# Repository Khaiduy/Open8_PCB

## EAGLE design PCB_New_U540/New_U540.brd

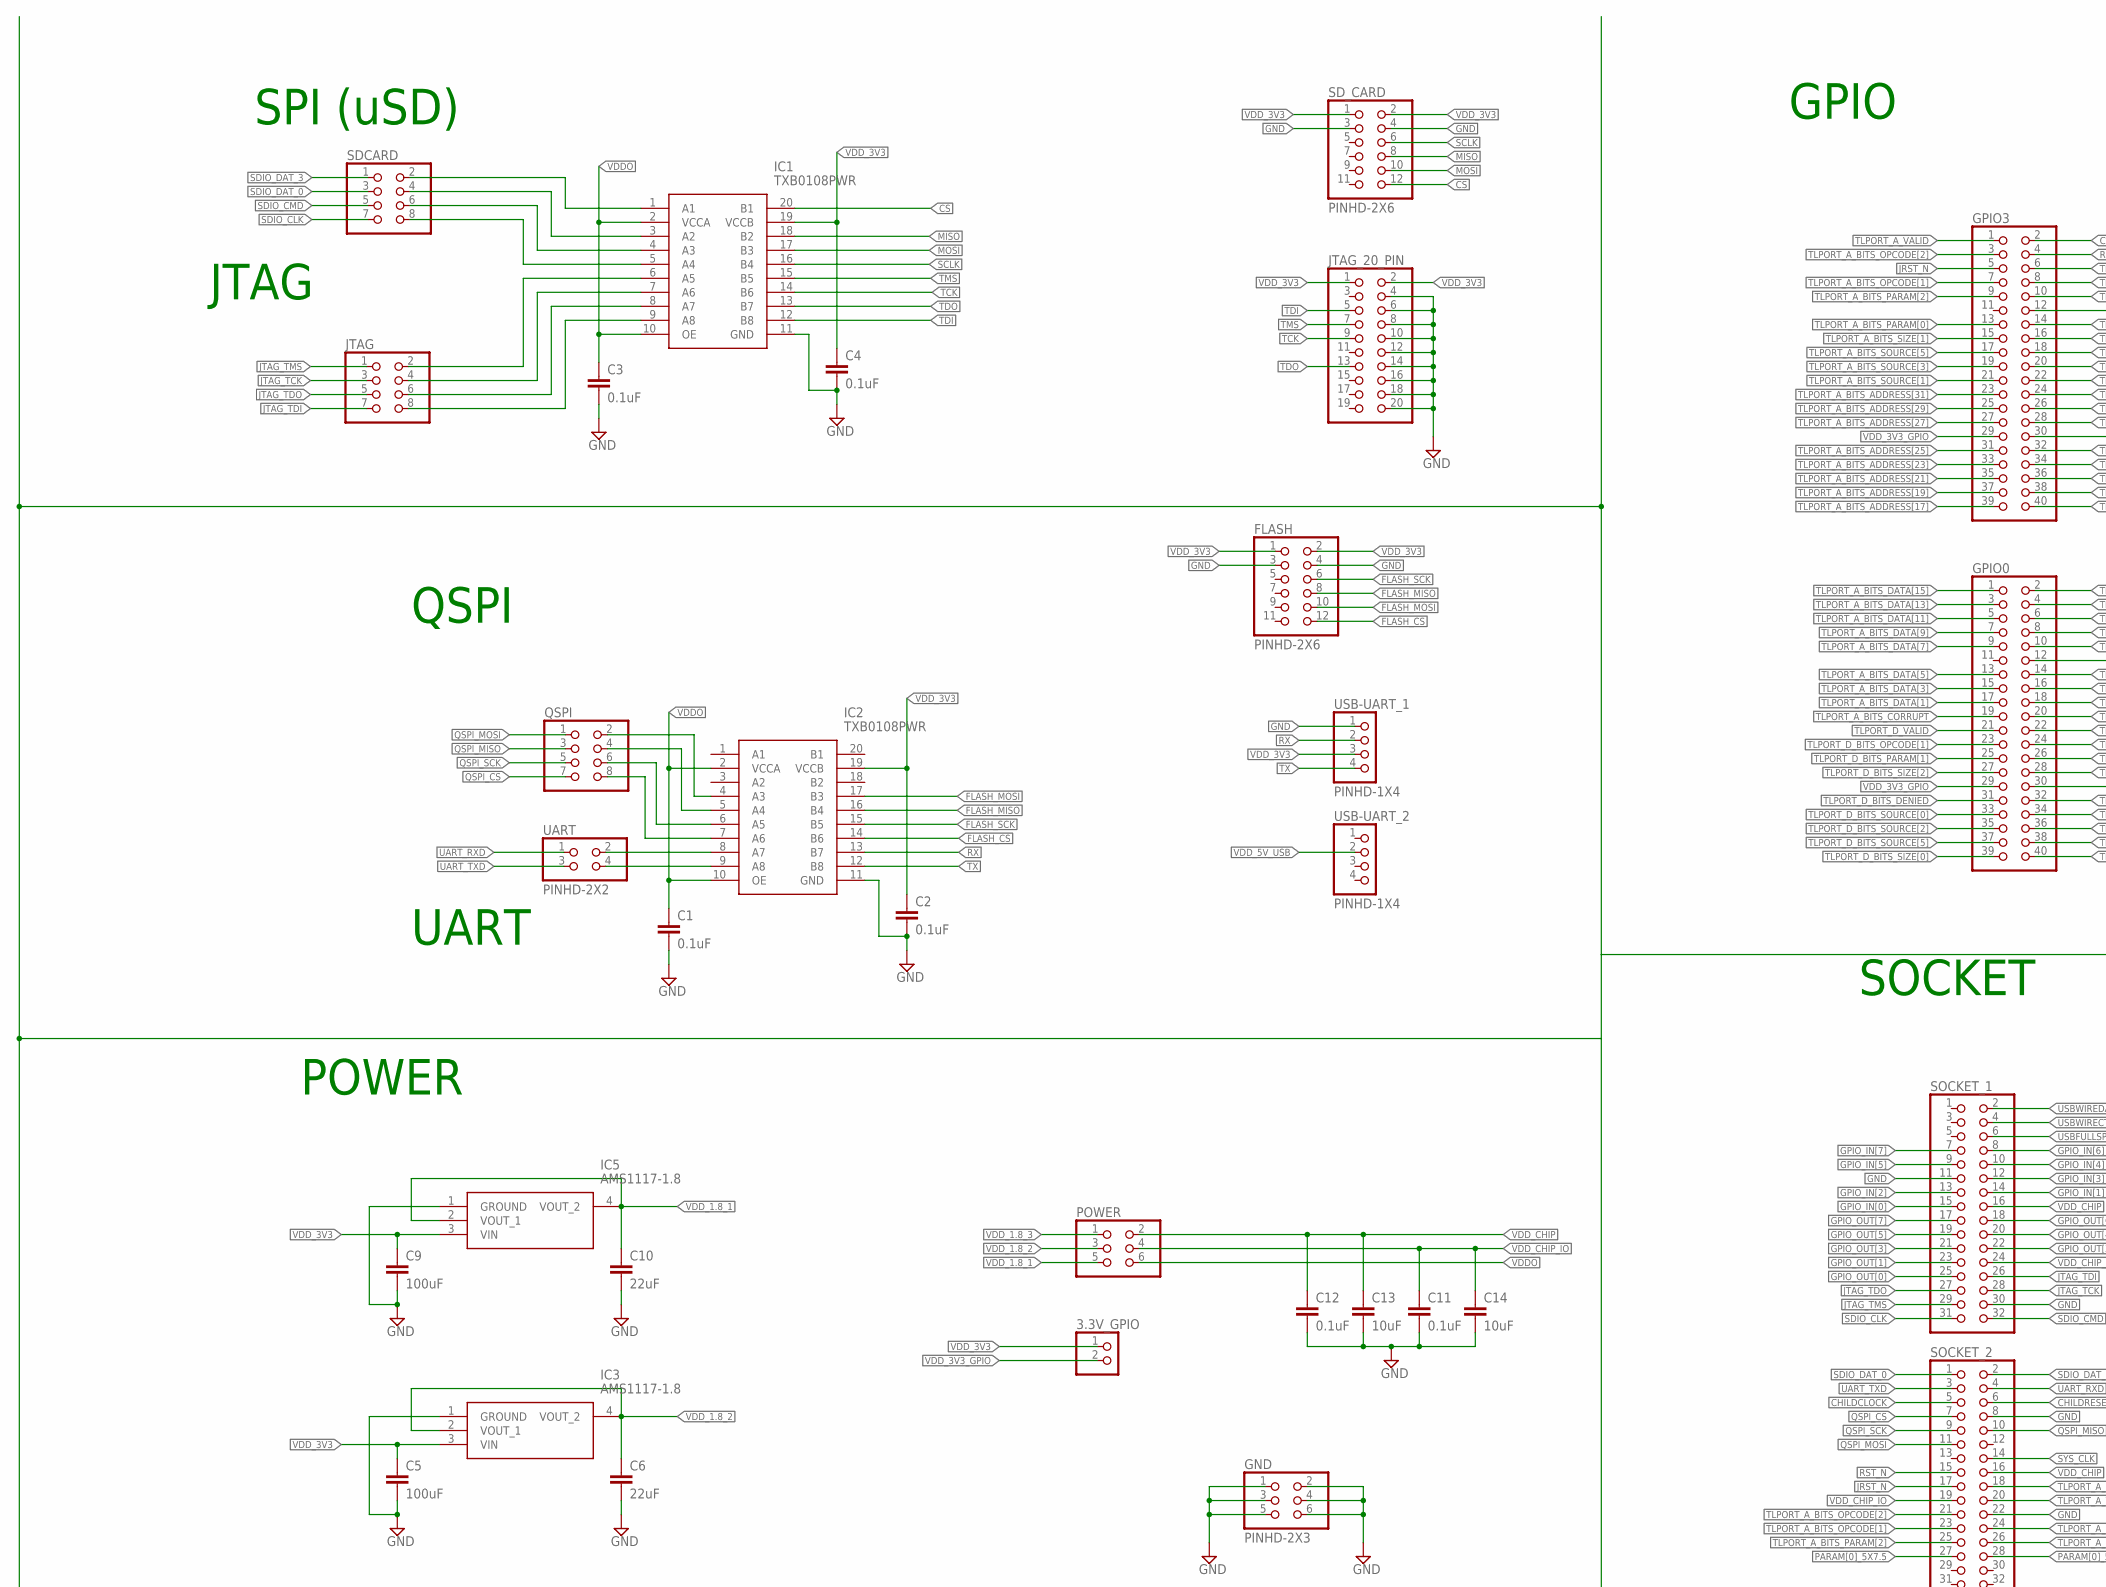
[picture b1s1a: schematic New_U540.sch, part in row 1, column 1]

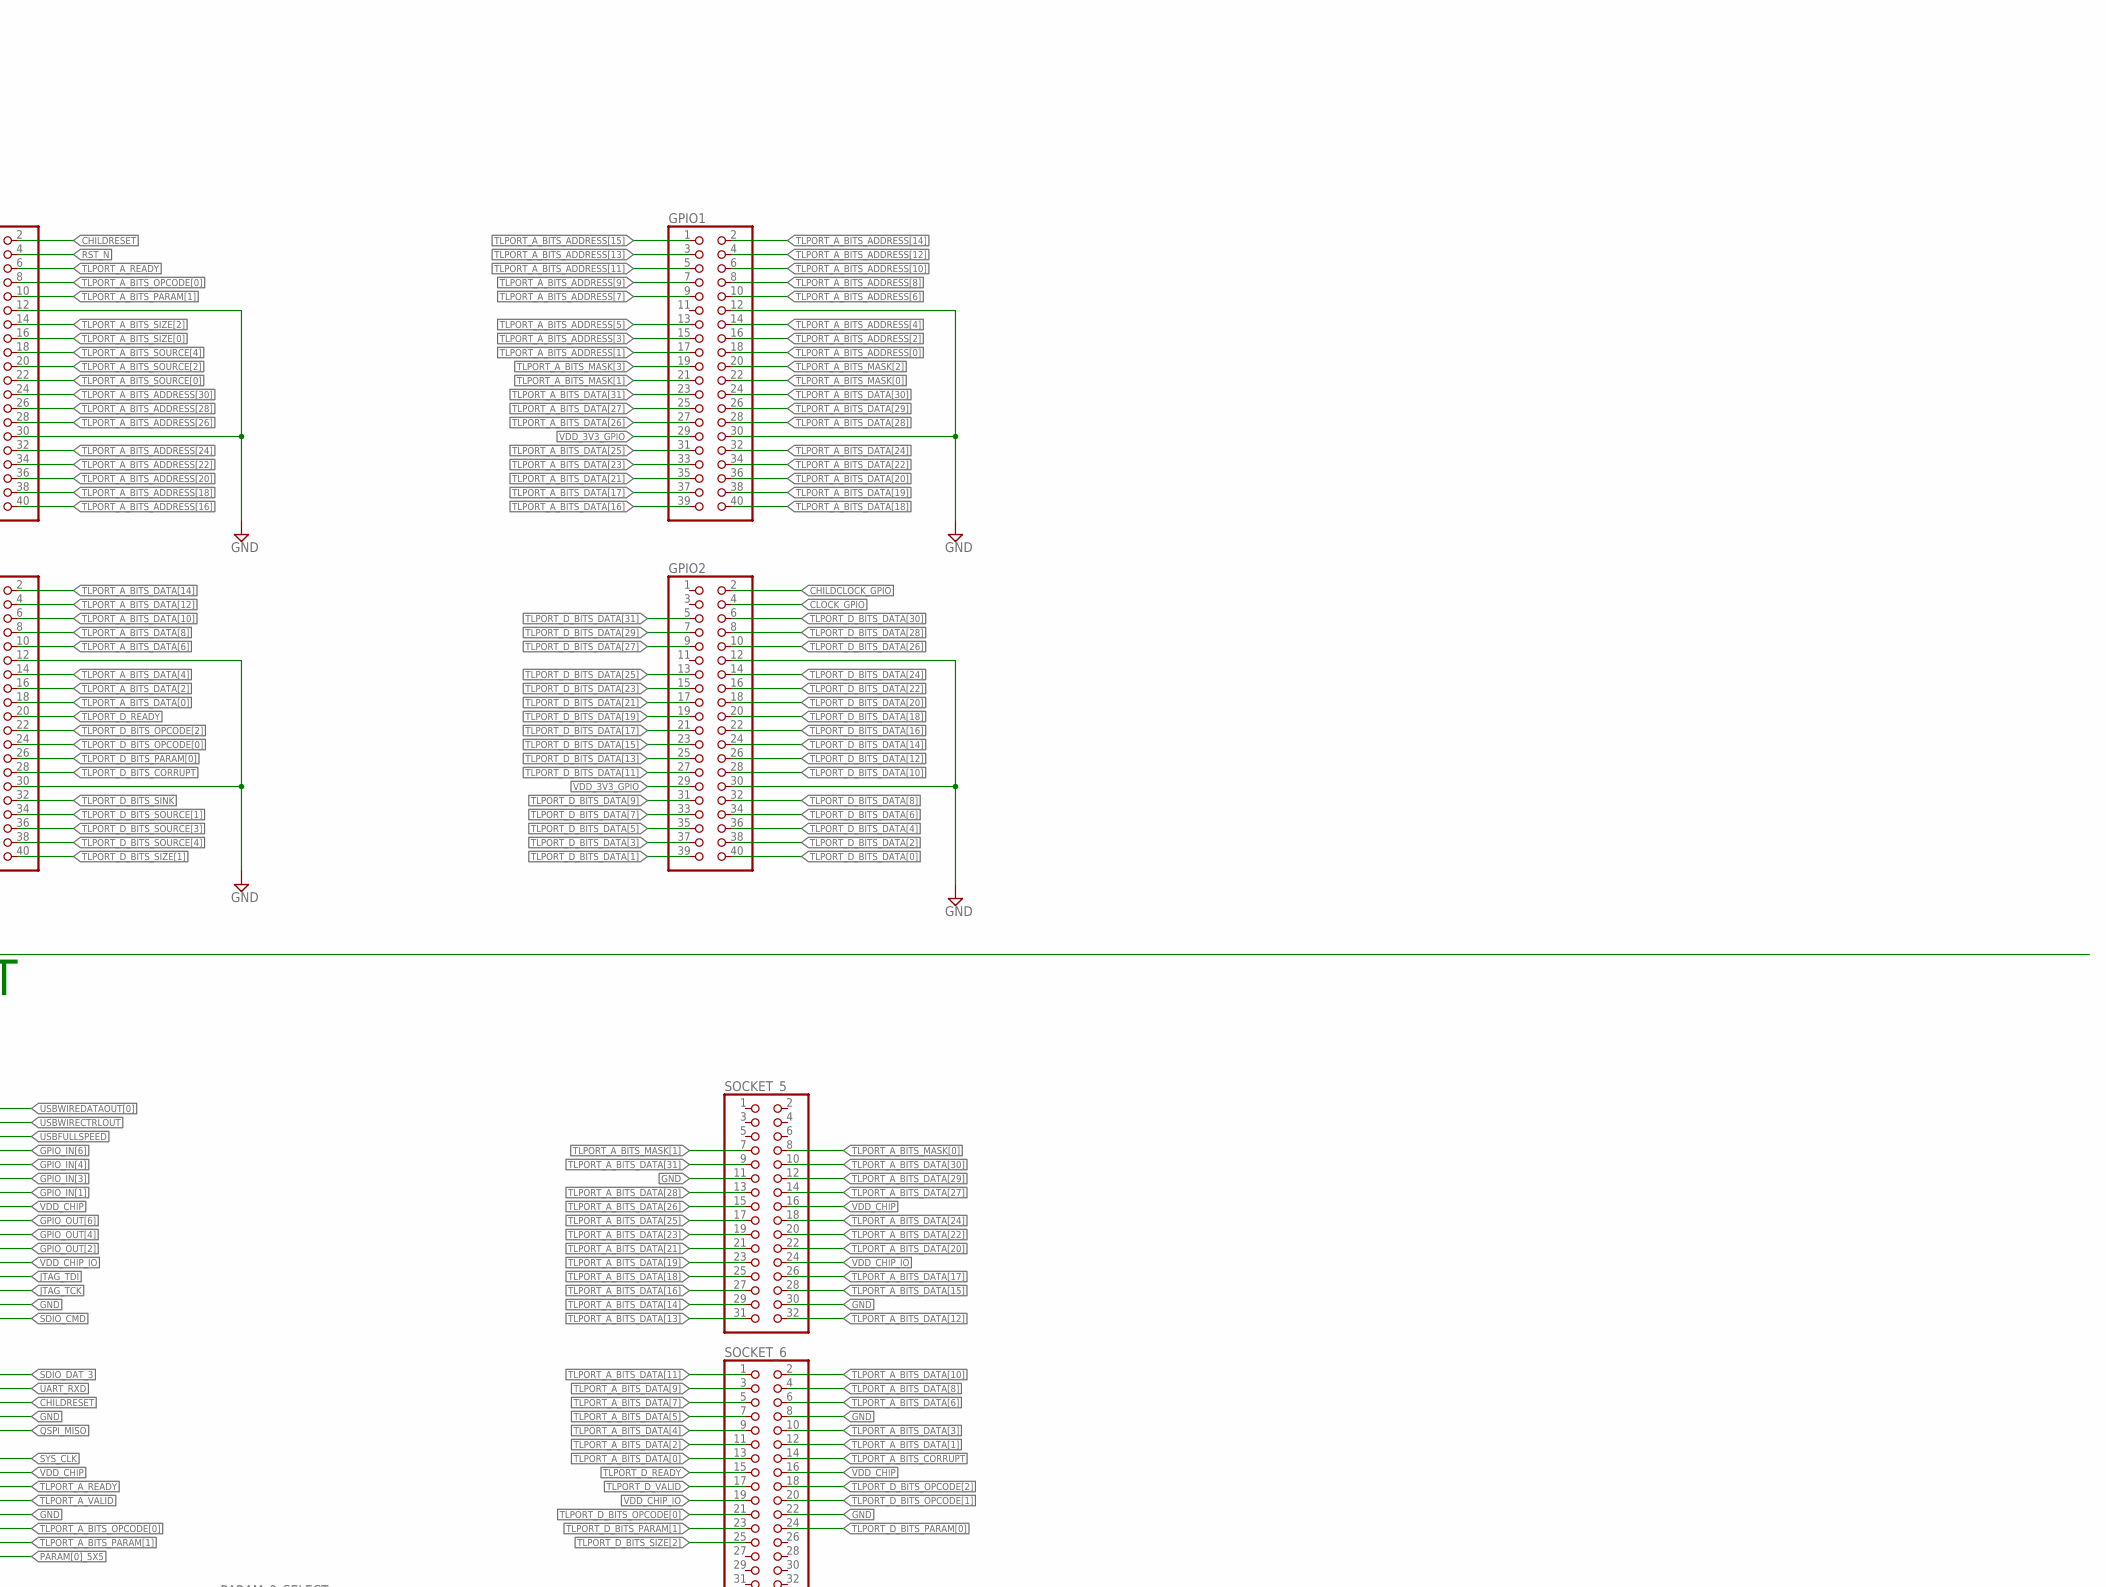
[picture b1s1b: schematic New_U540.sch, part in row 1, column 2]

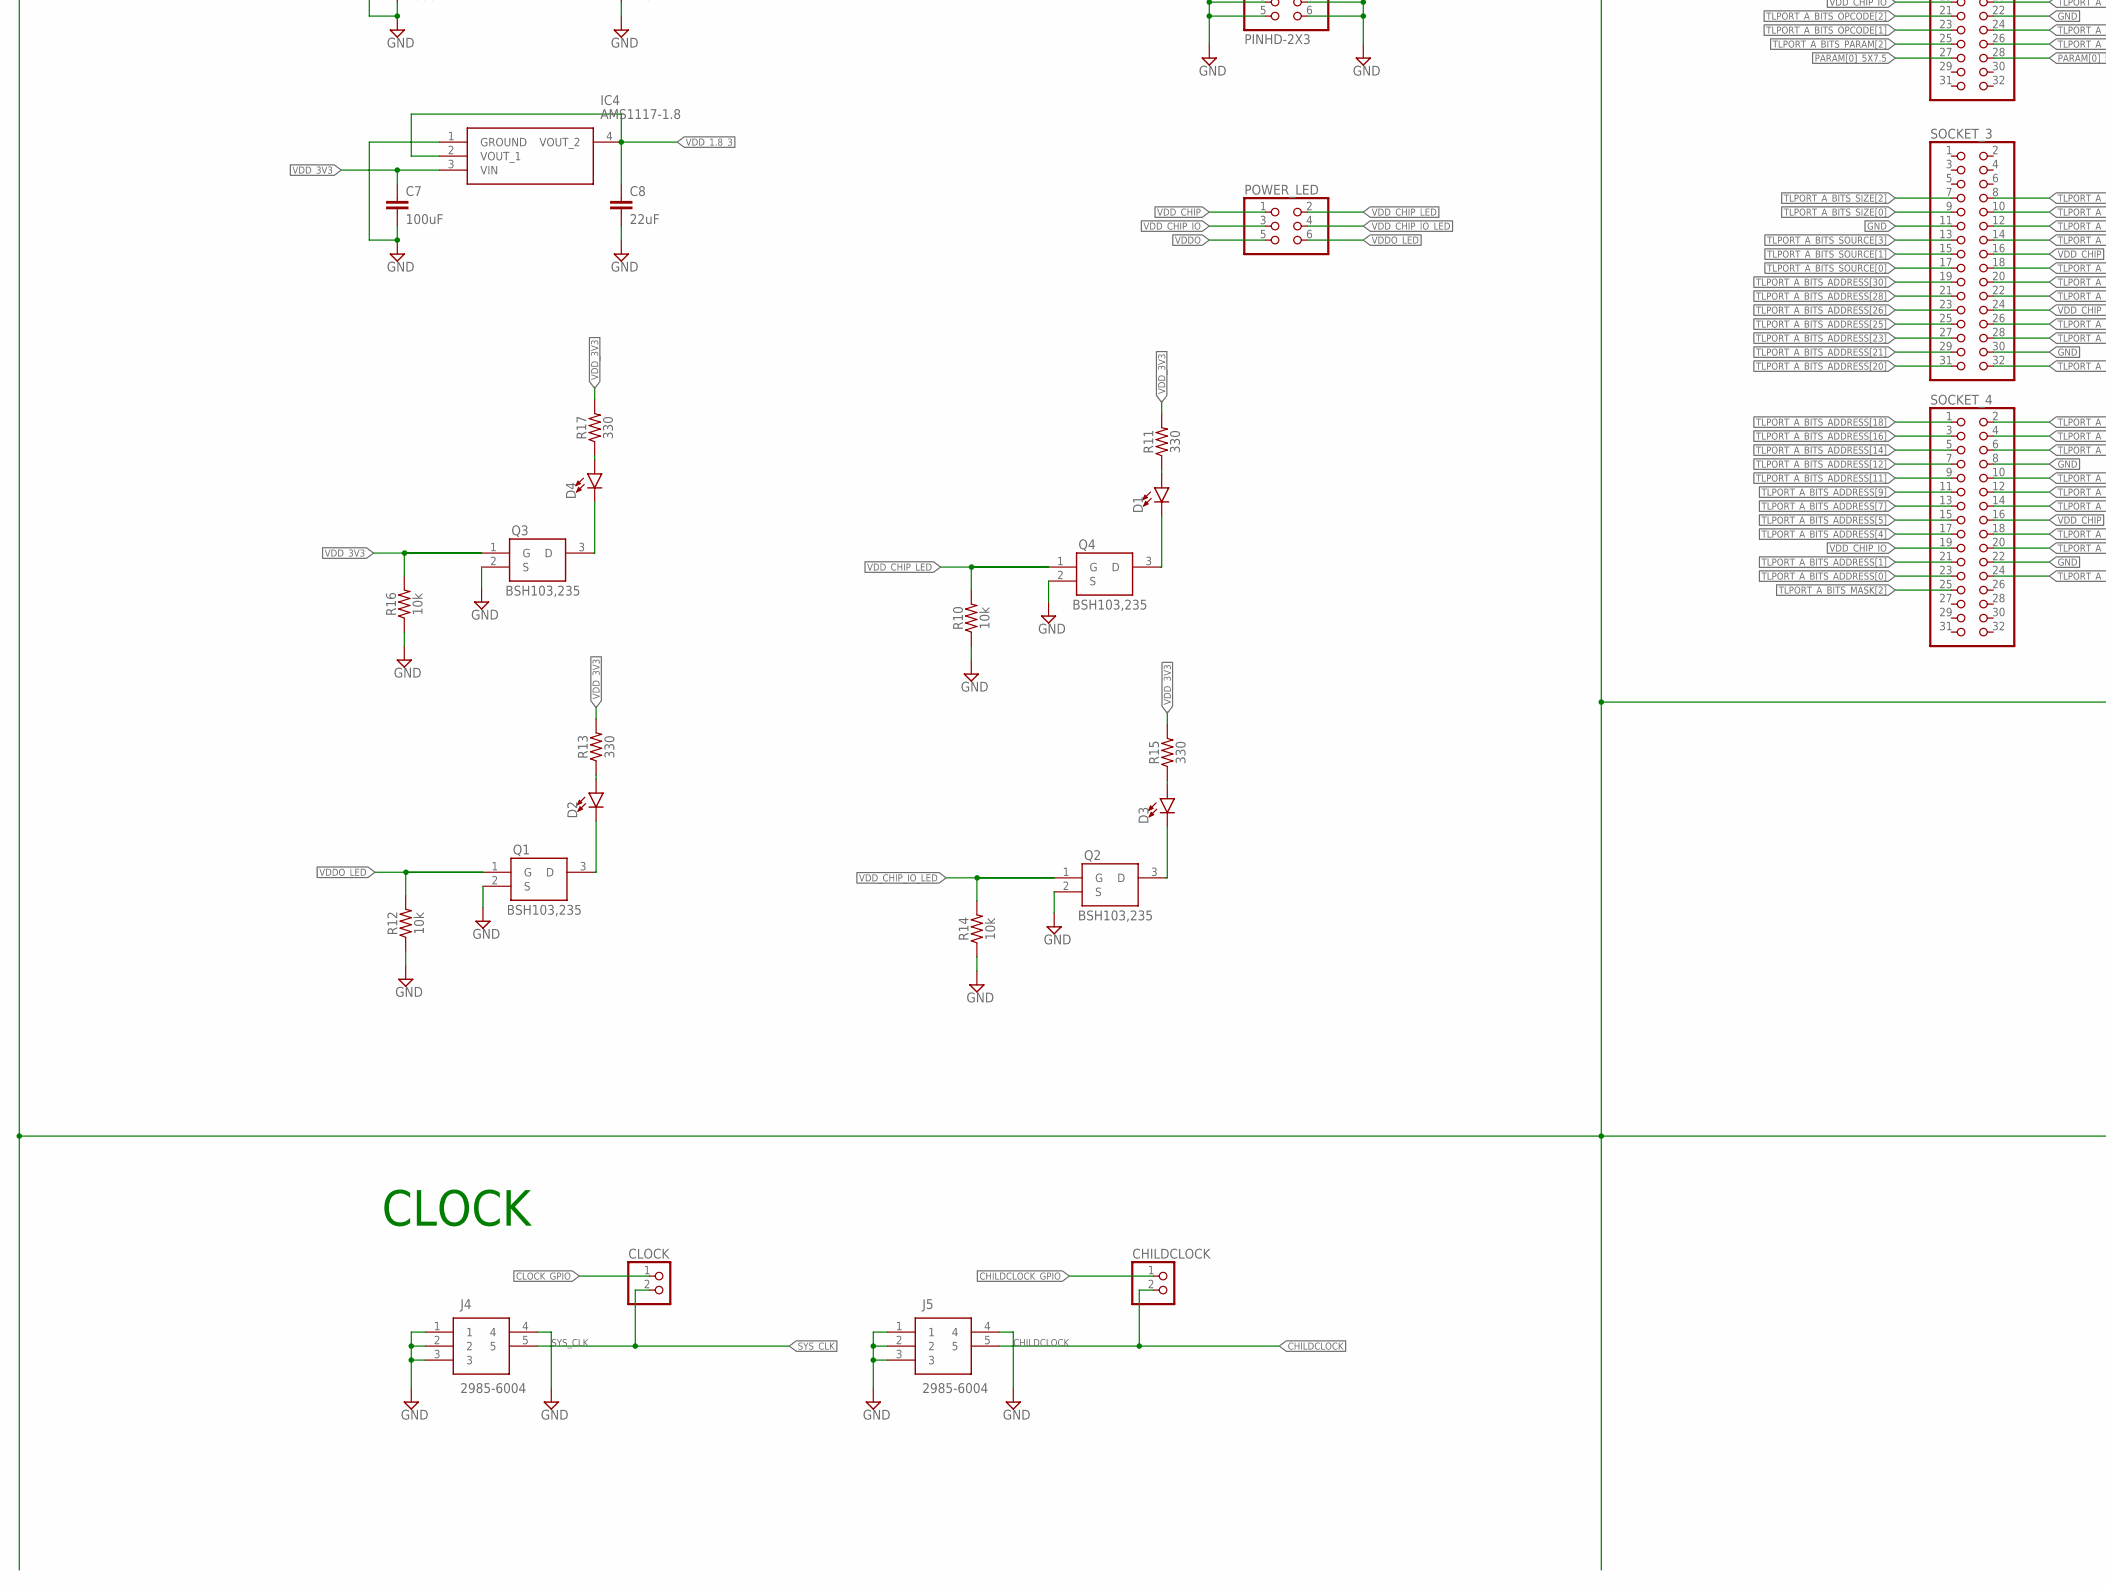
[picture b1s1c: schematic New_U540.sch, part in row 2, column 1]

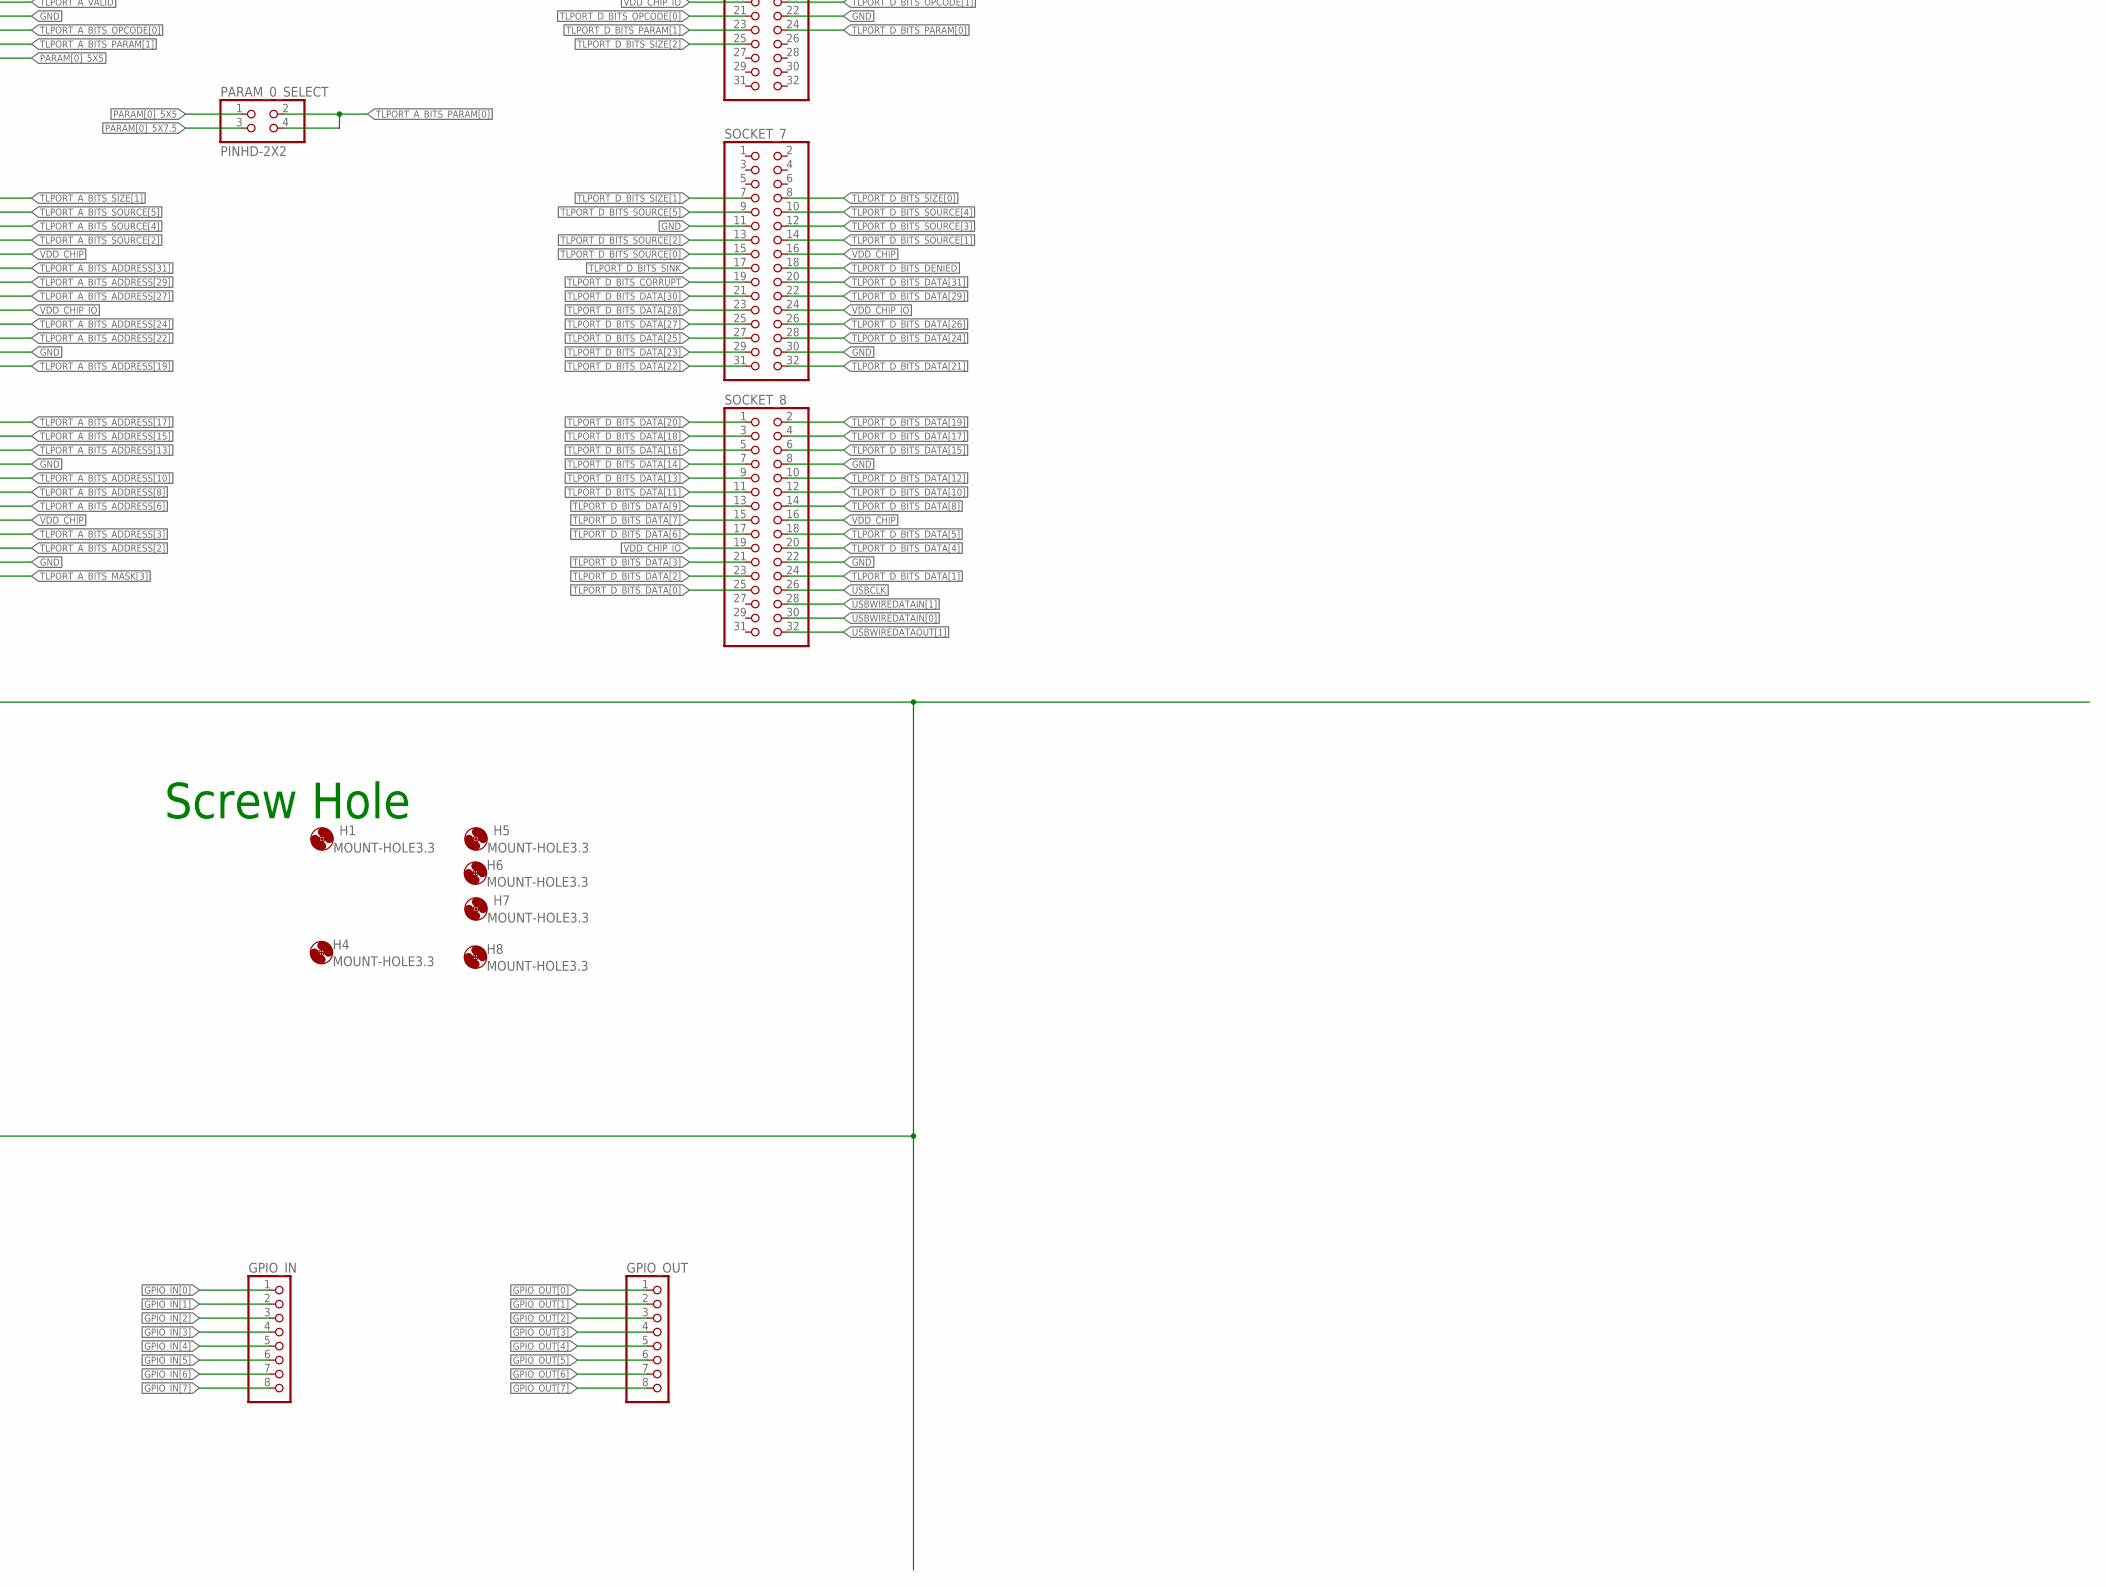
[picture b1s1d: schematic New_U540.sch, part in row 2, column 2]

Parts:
3.3V_GPIO: PINHD-1X2; 1X02
C1, C2, C3, C4, C11, C12: 0.1uF; 1206
C5, C7, C9: 100uF; 1206
C6, C8, C10: 22uF; 1206
C13, C14: 10uF; 1206
CHILDCLOCK: PINHD-1X2; 1X02
CLOCK: PINHD-1X2; 1X02
D1, D2, D3, D4: LED1206; LED-1206
FLASH: PINHD-2X6; 2X06
GND: PINHD-2X3; 2X03
GPIO0, GPIO1, GPIO2, GPIO3: PINHD-2X20; 2X20
GPIO_IN: PINHD-1X8; 1X08
GPIO_OUT: PINHD-1X8; 1X08
H1, H4, H5, H6, H7, H8: MOUNT-HOLE3.3; 3,3
IC1, IC2: TXB0108PWR; SOP65P640X120-20N
IC3, IC4, IC5: AMS1117-1.8; SOT229P700X180-4N
J4, J5: 2985-6004; 29856004
JTAG: PINHD-2X4; 2X04
JTAG_20_PIN: PINHD-2X10; 2X10
PARAM_0_SELECT: PINHD-2X2; 2X02
POWER: PINHD-2X3; 2X03
POWER_LED: PINHD-2X3; 2X03
Q1, Q2, Q3, Q4: BSH103,235; SOT95P230X110-3N
QSPI: PINHD-2X4; 2X04
R10, R12, R14, R16: 10k; 1206
R11, R13, R15, R17: 330; 1206
SDCARD: PINHD-2X4; 2X04
SD_CARD: PINHD-2X6; 2X06
SOCKET_1, SOCKET_2, SOCKET_3, SOCKET_4, SOCKET_5, SOCKET_6, SOCKET_7, SOCKET_8: PINHD-2X16; 2X16
UART: PINHD-2X2; 2X02
USB-UART_1, USB-UART_2: PINHD-1X4; 1X04

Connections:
CHILDCLOCK: CHILDCLOCK.2, J5.5, SOCKET_2.5
CHILDCLOCK_GPIO: CHILDCLOCK.1, GPIO2.2
CHILDRESET: GPIO3.2, SOCKET_2.6
CLOCK_GPIO: CLOCK.1, GPIO2.4
CS: IC1.20 (B1), SD_CARD.12
FLASH_CS: FLASH.12, IC2.14 (B6)
FLASH_MISO: FLASH.8, IC2.16 (B4)
FLASH_MOSI: FLASH.10, IC2.17 (B3)
FLASH_SCK: FLASH.6, IC2.15 (B5)
GND: C1.2, C2.2, C3.2, C4.2, C5.2, C6.2, C7.2, C8.2, C9.2, C10.2, C11.2, C12.2, C13.2, C14.2, FLASH.3, FLASH.4, GND.1, GND.2, GND.3, GND.4, GND.5, GND.6, GPIO0.12, GPIO0.30, GPIO1.12, GPIO1.30, GPIO2.12, GPIO2.30, GPIO3.12, GPIO3.30, IC1.11 (GND), IC2.11 (GND), IC3.1 (GROUND), IC4.1 (GROUND), IC5.1 (GROUND), J4.1, J4.2, J4.3, J4.4, J5.1, J5.2, J5.3, J5.4, JTAG_20_PIN.4, JTAG_20_PIN.6, JTAG_20_PIN.8, JTAG_20_PIN.10, JTAG_20_PIN.12, JTAG_20_PIN.14, JTAG_20_PIN.16, JTAG_20_PIN.18, JTAG_20_PIN.20, Q1.2 (S), Q2.2 (S), Q3.2 (S), Q4.2 (S), R10.1, R12.1, R14.1, R16.1, SD_CARD.3, SD_CARD.4, SOCKET_1.11, SOCKET_1.30, SOCKET_2.8, SOCKET_2.22, SOCKET_3.11, SOCKET_3.30, SOCKET_4.8, SOCKET_4.22, SOCKET_5.11, SOCKET_5.30, SOCKET_6.8, SOCKET_6.22, SOCKET_7.11, SOCKET_7.30, SOCKET_8.8, SOCKET_8.22, USB-UART_1.1
GPIO_IN[0]: GPIO_IN.1, SOCKET_1.15
GPIO_IN[1]: GPIO_IN.2, SOCKET_1.14
GPIO_IN[2]: GPIO_IN.3, SOCKET_1.13
GPIO_IN[3]: GPIO_IN.4, SOCKET_1.12
GPIO_IN[4]: GPIO_IN.5, SOCKET_1.10
GPIO_IN[5]: GPIO_IN.6, SOCKET_1.9
GPIO_IN[6]: GPIO_IN.7, SOCKET_1.8
GPIO_IN[7]: GPIO_IN.8, SOCKET_1.7
GPIO_OUT[0]: GPIO_OUT.1, SOCKET_1.25
GPIO_OUT[1]: GPIO_OUT.2, SOCKET_1.23
GPIO_OUT[2]: GPIO_OUT.3, SOCKET_1.22
GPIO_OUT[3]: GPIO_OUT.4, SOCKET_1.21
GPIO_OUT[4]: GPIO_OUT.5, SOCKET_1.20
GPIO_OUT[5]: GPIO_OUT.6, SOCKET_1.19
GPIO_OUT[6]: GPIO_OUT.7, SOCKET_1.18
GPIO_OUT[7]: GPIO_OUT.8, SOCKET_1.17
JRST_N: GPIO3.5, SOCKET_2.17
JTAG_TCK: JTAG.3, SOCKET_1.28
JTAG_TDI: JTAG.7, SOCKET_1.26
JTAG_TDO: JTAG.5, SOCKET_1.27
JTAG_TMS: JTAG.1, SOCKET_1.29
MISO: IC1.18 (B2), SD_CARD.8
MOSI: IC1.17 (B3), SD_CARD.10
unnamed: IC1.1 (A1), SDCARD.2
unnamed: IC1.3 (A2), SDCARD.4
unnamed: IC1.4 (A3), SDCARD.6
unnamed: IC1.5 (A4), SDCARD.8
unnamed: IC2.9 (A8), UART.4
unnamed: IC2.8 (A7), UART.2
unnamed: IC1.9 (A8), JTAG.8
unnamed: IC1.8 (A7), JTAG.6
unnamed: IC1.7 (A6), JTAG.4
unnamed: IC1.6 (A5), JTAG.2
unnamed: IC2.7 (A6), QSPI.8
unnamed: IC2.6 (A5), QSPI.6
unnamed: IC2.5 (A4), QSPI.4
unnamed: IC2.4 (A3), QSPI.2
unnamed: D1.A, R11.1
unnamed: D2.A, R13.1
unnamed: D1.C, Q4.3 (D)
unnamed: D2.C, Q1.3 (D)
unnamed: D3.A, R15.1
unnamed: D3.C, Q2.3 (D)
unnamed: D4.A, R17.1
unnamed: D4.C, Q3.3 (D)
PARAM[0]_5X5: PARAM_0_SELECT.1, SOCKET_2.28
PARAM[0]_5X7.5: PARAM_0_SELECT.3, SOCKET_2.27
QSPI_CS: QSPI.7, SOCKET_2.7
QSPI_MISO: QSPI.3, SOCKET_2.10
QSPI_MOSI: QSPI.1, SOCKET_2.11
QSPI_SCK: QSPI.5, SOCKET_2.9
RST_N: GPIO3.4, SOCKET_2.15
RX: IC2.13 (B7), USB-UART_1.2
SCLK: IC1.16 (B4), SD_CARD.6
SDIO_CLK: SDCARD.7, SOCKET_1.31
SDIO_CMD: SDCARD.5, SOCKET_1.32
SDIO_DAT_0: SDCARD.3, SOCKET_2.1
SDIO_DAT_3: SDCARD.1, SOCKET_2.2
SYS_CLK: CLOCK.2, J4.5, SOCKET_2.14
TCK: IC1.14 (B6), JTAG_20_PIN.9
TDI: IC1.12 (B8), JTAG_20_PIN.5
TDO: IC1.13 (B7), JTAG_20_PIN.13
TLPORT_A_BITS_ADDRESS[0]: GPIO1.18, SOCKET_4.23
TLPORT_A_BITS_ADDRESS[1]: GPIO1.17, SOCKET_4.21
TLPORT_A_BITS_ADDRESS[2]: GPIO1.16, SOCKET_4.20
TLPORT_A_BITS_ADDRESS[3]: GPIO1.15, SOCKET_4.18
TLPORT_A_BITS_ADDRESS[4]: GPIO1.14, SOCKET_4.17
TLPORT_A_BITS_ADDRESS[5]: GPIO1.13, SOCKET_4.15
TLPORT_A_BITS_ADDRESS[6]: GPIO1.10, SOCKET_4.14
TLPORT_A_BITS_ADDRESS[7]: GPIO1.9, SOCKET_4.13
TLPORT_A_BITS_ADDRESS[8]: GPIO1.8, SOCKET_4.12
TLPORT_A_BITS_ADDRESS[9]: GPIO1.7, SOCKET_4.11
TLPORT_A_BITS_ADDRESS[10]: GPIO1.6, SOCKET_4.10
TLPORT_A_BITS_ADDRESS[11]: GPIO1.5, SOCKET_4.9
TLPORT_A_BITS_ADDRESS[12]: GPIO1.4, SOCKET_4.7
TLPORT_A_BITS_ADDRESS[13]: GPIO1.3, SOCKET_4.6
TLPORT_A_BITS_ADDRESS[14]: GPIO1.2, SOCKET_4.5
TLPORT_A_BITS_ADDRESS[15]: GPIO1.1, SOCKET_4.4
TLPORT_A_BITS_ADDRESS[16]: GPIO3.40, SOCKET_4.3
TLPORT_A_BITS_ADDRESS[17]: GPIO3.39, SOCKET_4.2
TLPORT_A_BITS_ADDRESS[18]: GPIO3.38, SOCKET_4.1
TLPORT_A_BITS_ADDRESS[19]: GPIO3.37, SOCKET_3.32
TLPORT_A_BITS_ADDRESS[20]: GPIO3.36, SOCKET_3.31
TLPORT_A_BITS_ADDRESS[21]: GPIO3.35, SOCKET_3.29
TLPORT_A_BITS_ADDRESS[22]: GPIO3.34, SOCKET_3.28
TLPORT_A_BITS_ADDRESS[23]: GPIO3.33, SOCKET_3.27
TLPORT_A_BITS_ADDRESS[24]: GPIO3.32, SOCKET_3.26
TLPORT_A_BITS_ADDRESS[25]: GPIO3.31, SOCKET_3.25
TLPORT_A_BITS_ADDRESS[26]: GPIO3.28, SOCKET_3.23
TLPORT_A_BITS_ADDRESS[27]: GPIO3.27, SOCKET_3.22
TLPORT_A_BITS_ADDRESS[28]: GPIO3.26, SOCKET_3.21
TLPORT_A_BITS_ADDRESS[29]: GPIO3.25, SOCKET_3.20
TLPORT_A_BITS_ADDRESS[30]: GPIO3.24, SOCKET_3.19
TLPORT_A_BITS_ADDRESS[31]: GPIO3.23, SOCKET_3.18
TLPORT_A_BITS_CORRUPT: GPIO0.19, SOCKET_6.14
TLPORT_A_BITS_DATA[0]: GPIO0.18, SOCKET_6.13
TLPORT_A_BITS_DATA[1]: GPIO0.17, SOCKET_6.12
TLPORT_A_BITS_DATA[2]: GPIO0.16, SOCKET_6.11
TLPORT_A_BITS_DATA[3]: GPIO0.15, SOCKET_6.10
TLPORT_A_BITS_DATA[4]: GPIO0.14, SOCKET_6.9
TLPORT_A_BITS_DATA[5]: GPIO0.13, SOCKET_6.7
TLPORT_A_BITS_DATA[6]: GPIO0.10, SOCKET_6.6
TLPORT_A_BITS_DATA[7]: GPIO0.9, SOCKET_6.5
TLPORT_A_BITS_DATA[8]: GPIO0.8, SOCKET_6.4
TLPORT_A_BITS_DATA[9]: GPIO0.7, SOCKET_6.3
TLPORT_A_BITS_DATA[10]: GPIO0.6, SOCKET_6.2
TLPORT_A_BITS_DATA[11]: GPIO0.5, SOCKET_6.1
TLPORT_A_BITS_DATA[12]: GPIO0.4, SOCKET_5.32
TLPORT_A_BITS_DATA[13]: GPIO0.3, SOCKET_5.31
TLPORT_A_BITS_DATA[14]: GPIO0.2, SOCKET_5.29
TLPORT_A_BITS_DATA[15]: GPIO0.1, SOCKET_5.28
TLPORT_A_BITS_DATA[16]: GPIO1.39, SOCKET_5.27
TLPORT_A_BITS_DATA[17]: GPIO1.37, SOCKET_5.26
TLPORT_A_BITS_DATA[18]: GPIO1.40, SOCKET_5.25
TLPORT_A_BITS_DATA[19]: GPIO1.38, SOCKET_5.23
TLPORT_A_BITS_DATA[20]: GPIO1.36, SOCKET_5.22
TLPORT_A_BITS_DATA[21]: GPIO1.35, SOCKET_5.21
TLPORT_A_BITS_DATA[22]: GPIO1.34, SOCKET_5.20
TLPORT_A_BITS_DATA[23]: GPIO1.33, SOCKET_5.19
TLPORT_A_BITS_DATA[24]: GPIO1.32, SOCKET_5.18
TLPORT_A_BITS_DATA[25]: GPIO1.31, SOCKET_5.17
TLPORT_A_BITS_DATA[26]: GPIO1.27, SOCKET_5.15
TLPORT_A_BITS_DATA[27]: GPIO1.25, SOCKET_5.14
TLPORT_A_BITS_DATA[28]: GPIO1.28, SOCKET_5.13
TLPORT_A_BITS_DATA[29]: GPIO1.26, SOCKET_5.12
TLPORT_A_BITS_DATA[30]: GPIO1.24, SOCKET_5.10
TLPORT_A_BITS_DATA[31]: GPIO1.23, SOCKET_5.9
TLPORT_A_BITS_MASK[0]: GPIO1.22, SOCKET_5.8
TLPORT_A_BITS_MASK[1]: GPIO1.21, SOCKET_5.7
TLPORT_A_BITS_MASK[2]: GPIO1.20, SOCKET_4.25
TLPORT_A_BITS_MASK[3]: GPIO1.19, SOCKET_4.24
TLPORT_A_BITS_OPCODE[0]: GPIO3.8, SOCKET_2.24
TLPORT_A_BITS_OPCODE[1]: GPIO3.7, SOCKET_2.23
TLPORT_A_BITS_OPCODE[2]: GPIO3.3, SOCKET_2.21
TLPORT_A_BITS_PARAM[0]: GPIO3.13, PARAM_0_SELECT.2, PARAM_0_SELECT.4
TLPORT_A_BITS_PARAM[1]: GPIO3.10, SOCKET_2.26
TLPORT_A_BITS_PARAM[2]: GPIO3.9, SOCKET_2.25
TLPORT_A_BITS_SIZE[0]: GPIO3.16, SOCKET_3.9
TLPORT_A_BITS_SIZE[1]: GPIO3.15, SOCKET_3.8
TLPORT_A_BITS_SIZE[2]: GPIO3.14, SOCKET_3.7
TLPORT_A_BITS_SOURCE[0]: GPIO3.22, SOCKET_3.17
TLPORT_A_BITS_SOURCE[1]: GPIO3.21, SOCKET_3.15
TLPORT_A_BITS_SOURCE[2]: GPIO3.20, SOCKET_3.14
TLPORT_A_BITS_SOURCE[3]: GPIO3.19, SOCKET_3.13
TLPORT_A_BITS_SOURCE[4]: GPIO3.18, SOCKET_3.12
TLPORT_A_BITS_SOURCE[5]: GPIO3.17, SOCKET_3.10
TLPORT_A_READY: GPIO3.6, SOCKET_2.18
TLPORT_A_VALID: GPIO3.1, SOCKET_2.20
TLPORT_D_BITS_CORRUPT: GPIO0.28, SOCKET_7.19
TLPORT_D_BITS_DATA[0]: GPIO2.40, SOCKET_8.25
TLPORT_D_BITS_DATA[1]: GPIO2.39, SOCKET_8.24
TLPORT_D_BITS_DATA[2]: GPIO2.38, SOCKET_8.23
TLPORT_D_BITS_DATA[3]: GPIO2.37, SOCKET_8.21
TLPORT_D_BITS_DATA[4]: GPIO2.36, SOCKET_8.20
TLPORT_D_BITS_DATA[5]: GPIO2.35, SOCKET_8.18
TLPORT_D_BITS_DATA[6]: GPIO2.34, SOCKET_8.17
TLPORT_D_BITS_DATA[7]: GPIO2.33, SOCKET_8.15
TLPORT_D_BITS_DATA[8]: GPIO2.32, SOCKET_8.14
TLPORT_D_BITS_DATA[9]: GPIO2.31, SOCKET_8.13
TLPORT_D_BITS_DATA[10]: GPIO2.28, SOCKET_8.12
TLPORT_D_BITS_DATA[11]: GPIO2.27, SOCKET_8.11
TLPORT_D_BITS_DATA[12]: GPIO2.26, SOCKET_8.10
TLPORT_D_BITS_DATA[13]: GPIO2.25, SOCKET_8.9
TLPORT_D_BITS_DATA[14]: GPIO2.24, SOCKET_8.7
TLPORT_D_BITS_DATA[15]: GPIO2.23, SOCKET_8.6
TLPORT_D_BITS_DATA[16]: GPIO2.22, SOCKET_8.5
TLPORT_D_BITS_DATA[17]: GPIO2.21, SOCKET_8.4
TLPORT_D_BITS_DATA[18]: GPIO2.20, SOCKET_8.3
TLPORT_D_BITS_DATA[19]: GPIO2.19, SOCKET_8.2
TLPORT_D_BITS_DATA[20]: GPIO2.18, SOCKET_8.1
TLPORT_D_BITS_DATA[21]: GPIO2.17, SOCKET_7.32
TLPORT_D_BITS_DATA[22]: GPIO2.16, SOCKET_7.31
TLPORT_D_BITS_DATA[23]: GPIO2.15, SOCKET_7.29
TLPORT_D_BITS_DATA[24]: GPIO2.14, SOCKET_7.28
TLPORT_D_BITS_DATA[25]: GPIO2.13, SOCKET_7.27
TLPORT_D_BITS_DATA[26]: GPIO2.10, SOCKET_7.26
TLPORT_D_BITS_DATA[27]: GPIO2.9, SOCKET_7.25
TLPORT_D_BITS_DATA[28]: GPIO2.8, SOCKET_7.23
TLPORT_D_BITS_DATA[29]: GPIO2.7, SOCKET_7.22
TLPORT_D_BITS_DATA[30]: GPIO2.6, SOCKET_7.21
TLPORT_D_BITS_DATA[31]: GPIO2.5, SOCKET_7.20
TLPORT_D_BITS_DENIED: GPIO0.31, SOCKET_7.18
TLPORT_D_BITS_OPCODE[0]: GPIO0.24, SOCKET_6.21
TLPORT_D_BITS_OPCODE[1]: GPIO0.23, SOCKET_6.20
TLPORT_D_BITS_OPCODE[2]: GPIO0.22, SOCKET_6.18
TLPORT_D_BITS_PARAM[0]: GPIO0.26, SOCKET_6.24
TLPORT_D_BITS_PARAM[1]: GPIO0.25, SOCKET_6.23
TLPORT_D_BITS_SINK: GPIO0.32, SOCKET_7.17
TLPORT_D_BITS_SIZE[0]: GPIO0.39, SOCKET_7.8
TLPORT_D_BITS_SIZE[1]: GPIO0.40, SOCKET_7.7
TLPORT_D_BITS_SIZE[2]: GPIO0.27, SOCKET_6.25
TLPORT_D_BITS_SOURCE[0]: GPIO0.33, SOCKET_7.15
TLPORT_D_BITS_SOURCE[1]: GPIO0.34, SOCKET_7.14
TLPORT_D_BITS_SOURCE[2]: GPIO0.35, SOCKET_7.13
TLPORT_D_BITS_SOURCE[3]: GPIO0.36, SOCKET_7.12
TLPORT_D_BITS_SOURCE[4]: GPIO0.38, SOCKET_7.10
TLPORT_D_BITS_SOURCE[5]: GPIO0.37, SOCKET_7.9
TLPORT_D_READY: GPIO0.20, SOCKET_6.15
TLPORT_D_VALID: GPIO0.21, SOCKET_6.17
TMS: IC1.15 (B5), JTAG_20_PIN.7
TX: IC2.12 (B8), USB-UART_1.4
UART_RXD: SOCKET_2.4, UART.1
UART_TXD: SOCKET_2.3, UART.3
USBCLK: SOCKET_8.26
USBFULLSPEED: SOCKET_1.6
USBWIRECTRLOUT: SOCKET_1.4
USBWIREDATAIN[0]: SOCKET_8.30
USBWIREDATAIN[1]: SOCKET_8.28
USBWIREDATAOUT[0]: SOCKET_1.2
USBWIREDATAOUT[1]: SOCKET_8.32
VDDO: C1.1, C3.1, IC1.2 (VCCA), IC1.10 (OE), IC2.2 (VCCA), IC2.10 (OE), POWER.6, POWER_LED.5
VDDO_LED: POWER_LED.6, Q1.1 (G), R12.2
VDD_1.8_1: C10.1, IC5.2 (VOUT_1), IC5.4 (VOUT_2), POWER.5
VDD_1.8_2: C6.1, IC3.2 (VOUT_1), IC3.4 (VOUT_2), POWER.3
VDD_1.8_3: C8.1, IC4.2 (VOUT_1), IC4.4 (VOUT_2), POWER.1
VDD_3V3: 3.3V_GPIO.1, C2.1, C4.1, C5.1, C7.1, C9.1, FLASH.1, FLASH.2, IC1.19 (VCCB), IC2.19 (VCCB), IC3.3 (VIN), IC4.3 (VIN), IC5.3 (VIN), JTAG_20_PIN.1, JTAG_20_PIN.2, Q3.1 (G), R11.2, R13.2, R15.2, R16.2, R17.2, SD_CARD.1, SD_CARD.2, USB-UART_1.3
VDD_3V3_GPIO: 3.3V_GPIO.2, GPIO0.29, GPIO1.29, GPIO2.29, GPIO3.29
VDD_5V_USB: USB-UART_2.2
VDD_CHIP: C12.1, C13.1, POWER.2, POWER_LED.1, SOCKET_1.16, SOCKET_2.16, SOCKET_3.16, SOCKET_4.16, SOCKET_5.16, SOCKET_6.16, SOCKET_7.16, SOCKET_8.16
VDD_CHIP_IO: C11.1, C14.1, POWER.4, POWER_LED.3, SOCKET_1.24, SOCKET_2.19, SOCKET_3.24, SOCKET_4.19, SOCKET_5.24, SOCKET_6.19, SOCKET_7.24, SOCKET_8.19
VDD_CHIP_IO_LED: POWER_LED.4, Q2.1 (G), R14.2
VDD_CHIP_LED: POWER_LED.2, Q4.1 (G), R10.2

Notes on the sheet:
QSPI
SPI (uSD)
CLOCK
POWER
SOCKET
GPIO
Screw Hole
JTAG
UART

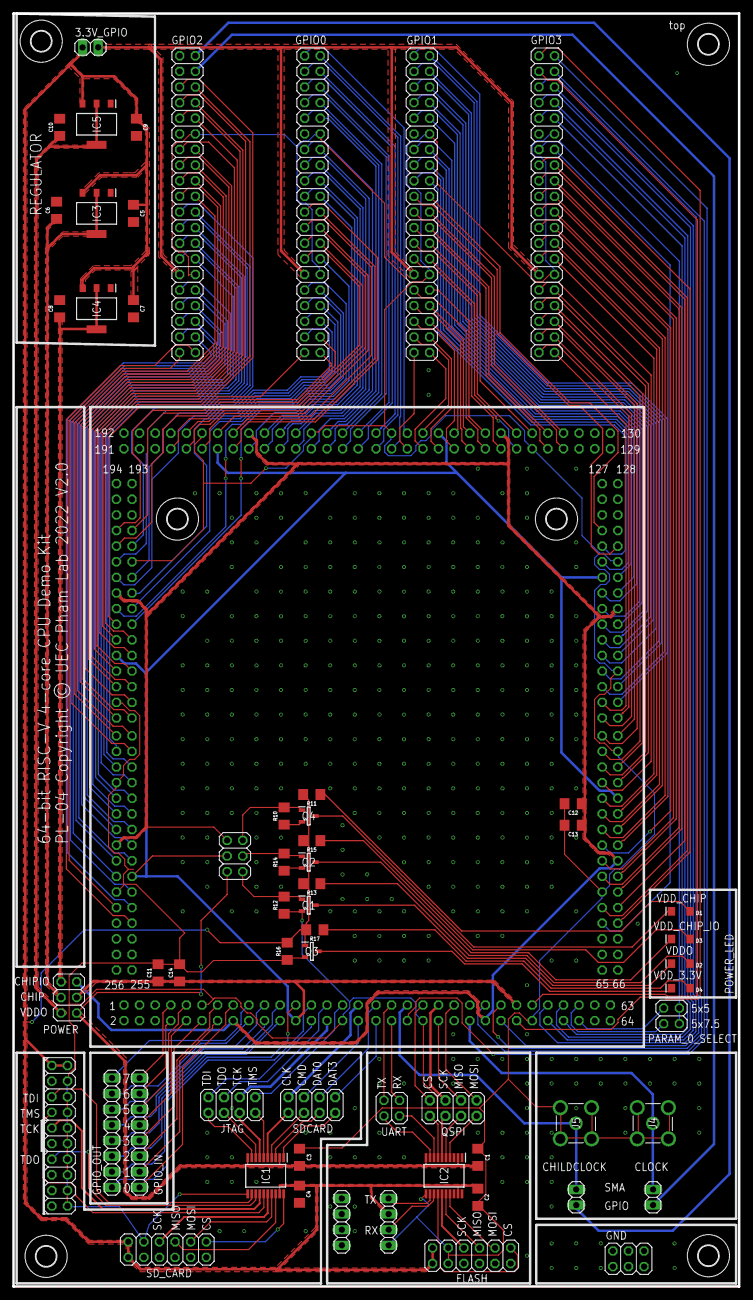
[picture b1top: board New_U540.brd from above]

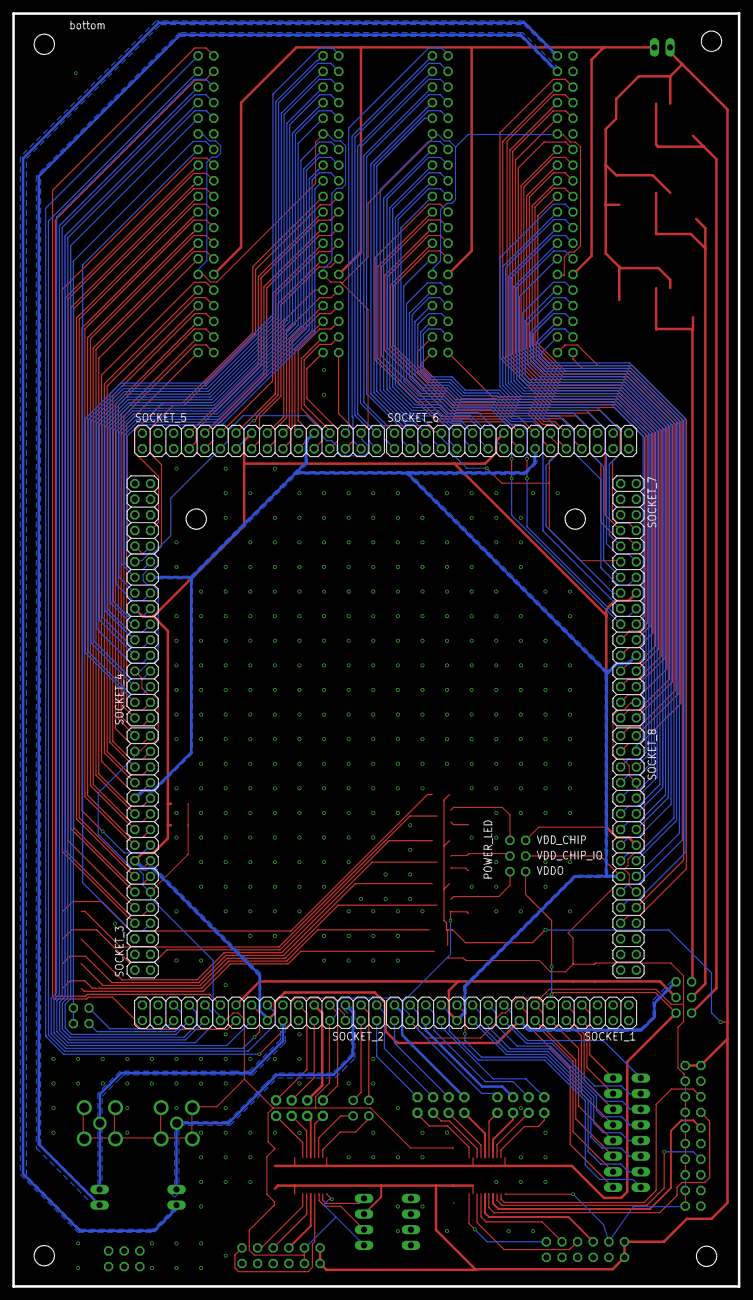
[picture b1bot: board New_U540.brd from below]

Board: 2 copper layers, 118.0 x 207.0 mm, 73 parts (8 on the bottom side), 224 nets.

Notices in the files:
PCB_New_U540/New_U540.brd:
PL-04 Copyright © UEC Pham Lab 2022 V2.0
PCB_ROHM_BaAnh/PCB_ROHM_BaAnh.brd:
Copyright © UEC PHAM LAB 2021
QFP160_new_socket/qfp160_socket_new.brd:
Copyright © Pham Lab 2021
TR4_PGA257(v4.0)/PGA257_socket.brd:
Copyright © UEC Pham Lab 2021 V1.0
TR4_PGA257(v4.0)/ROHM_PCB_thuc/TR4.brd:
PL-04 Copyright © UEC Pham Lab 2021 V1.0
parts and their libraries:
SparkFun-Resistors: Licensing: Creative Commons ShareAlike 4.0 International - https://creativecommons.org/licenses/by-sa/4.0
